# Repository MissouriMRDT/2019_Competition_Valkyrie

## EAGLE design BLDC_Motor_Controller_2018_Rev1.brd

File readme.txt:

https://www.amazon.com/RunCam-Camera-600TVL-Blocked-Quadcopter/dp/B06XW93GM9/ref=sr_1_5?s=electronics&ie=UTF8&qid=1522101421&sr=1-5&keywords=runcam

/////////////////////////////////////////////////////////////
// 3 Pin Picoblade twisted pair FPV:

// 1 => yellow => composite video (0.000v to 1.073v peak)
// 2 => black  => ground (0v)
// 3 => red    => 12v

/////////////////////////////////////////////////////////////
// 2 Pin BNC video:

// 1 => tip => composite video (0.000v to 1.073v peak)
// 2 => sleeve  => ground (0v)

https://www.digikey.com/product-detail/en/te-connectivity-amp-connectors/1-1478032-0/A97560-ND/1755947

/////////////////////////////////////////////////////////////
// 2 Pin RCA video (yellow)

// 1 => tip => composite video (0.000v to 1.073v peak)
// 2 => sleeve  => ground (0v)

https://www.digikey.com/product-detail/en/switchcraft-inc/PJRAN1X1U04X/PJRAN1X1U04X-ND/969899
http://www.switchcraft.com/Drawings/pjran1x1u__x_series_cd.pdf

/////////////////////////////////////////////////////////////
// 2 Pin barrel jack (2.1mm by 5.5mm center positive)

// 1 => center => 12v positive
// 2 => sleeve  => ground (0v)

https://www.digikey.com/product-detail/en/mpd-memory-protection-devices/EJ508A/EJ508A-ND/2439547

////////////////////////////////////////////////////////////////////////////////////////////////////

https://www.digikey.com/product-detail/en/texas-instruments/LMH6574MA-NOPB/LMH6574MA-NOPB-ND/700454
https://www.digikey.com/product-detail/en/texas-instruments/TXB0102DCUR/296-22862-1-ND/1740009

http://www.ti.com/lit/ds/symlink/lmh6574.pdf
http://www.ti.com/lit/ds/symlink/txb0102.pdf

//////////////////////////////////////////////////////////////////////////////////////////////////////////////////////////////

https://www.propwashed.com/quadcopter-connector-guide/
https://www.propwashed.com/fpv-camera-buyers-guide/
https://www.cctv-information.co.uk/i/Transmission_of_Video_Signals

https://www.digikey.com/en/ptm/t/texas-instruments/introduction-to-level-translation/tutorial
https://www.digikey.com/en/ptm/t/texas-instruments/amplifiers-high-speed-amplifiers-for-video-applications---part-1/tutorial
https://www.digikey.com/en/ptm/t/texas-instruments/amplifiers-high-speed-amplifiers-for-video-applications---part-2/tutorial
https://www.digikey.com/en/ptm/t/texas-instruments/amplifiers-high-speed-amplifiers-for-video-applications---part-3/tutorial

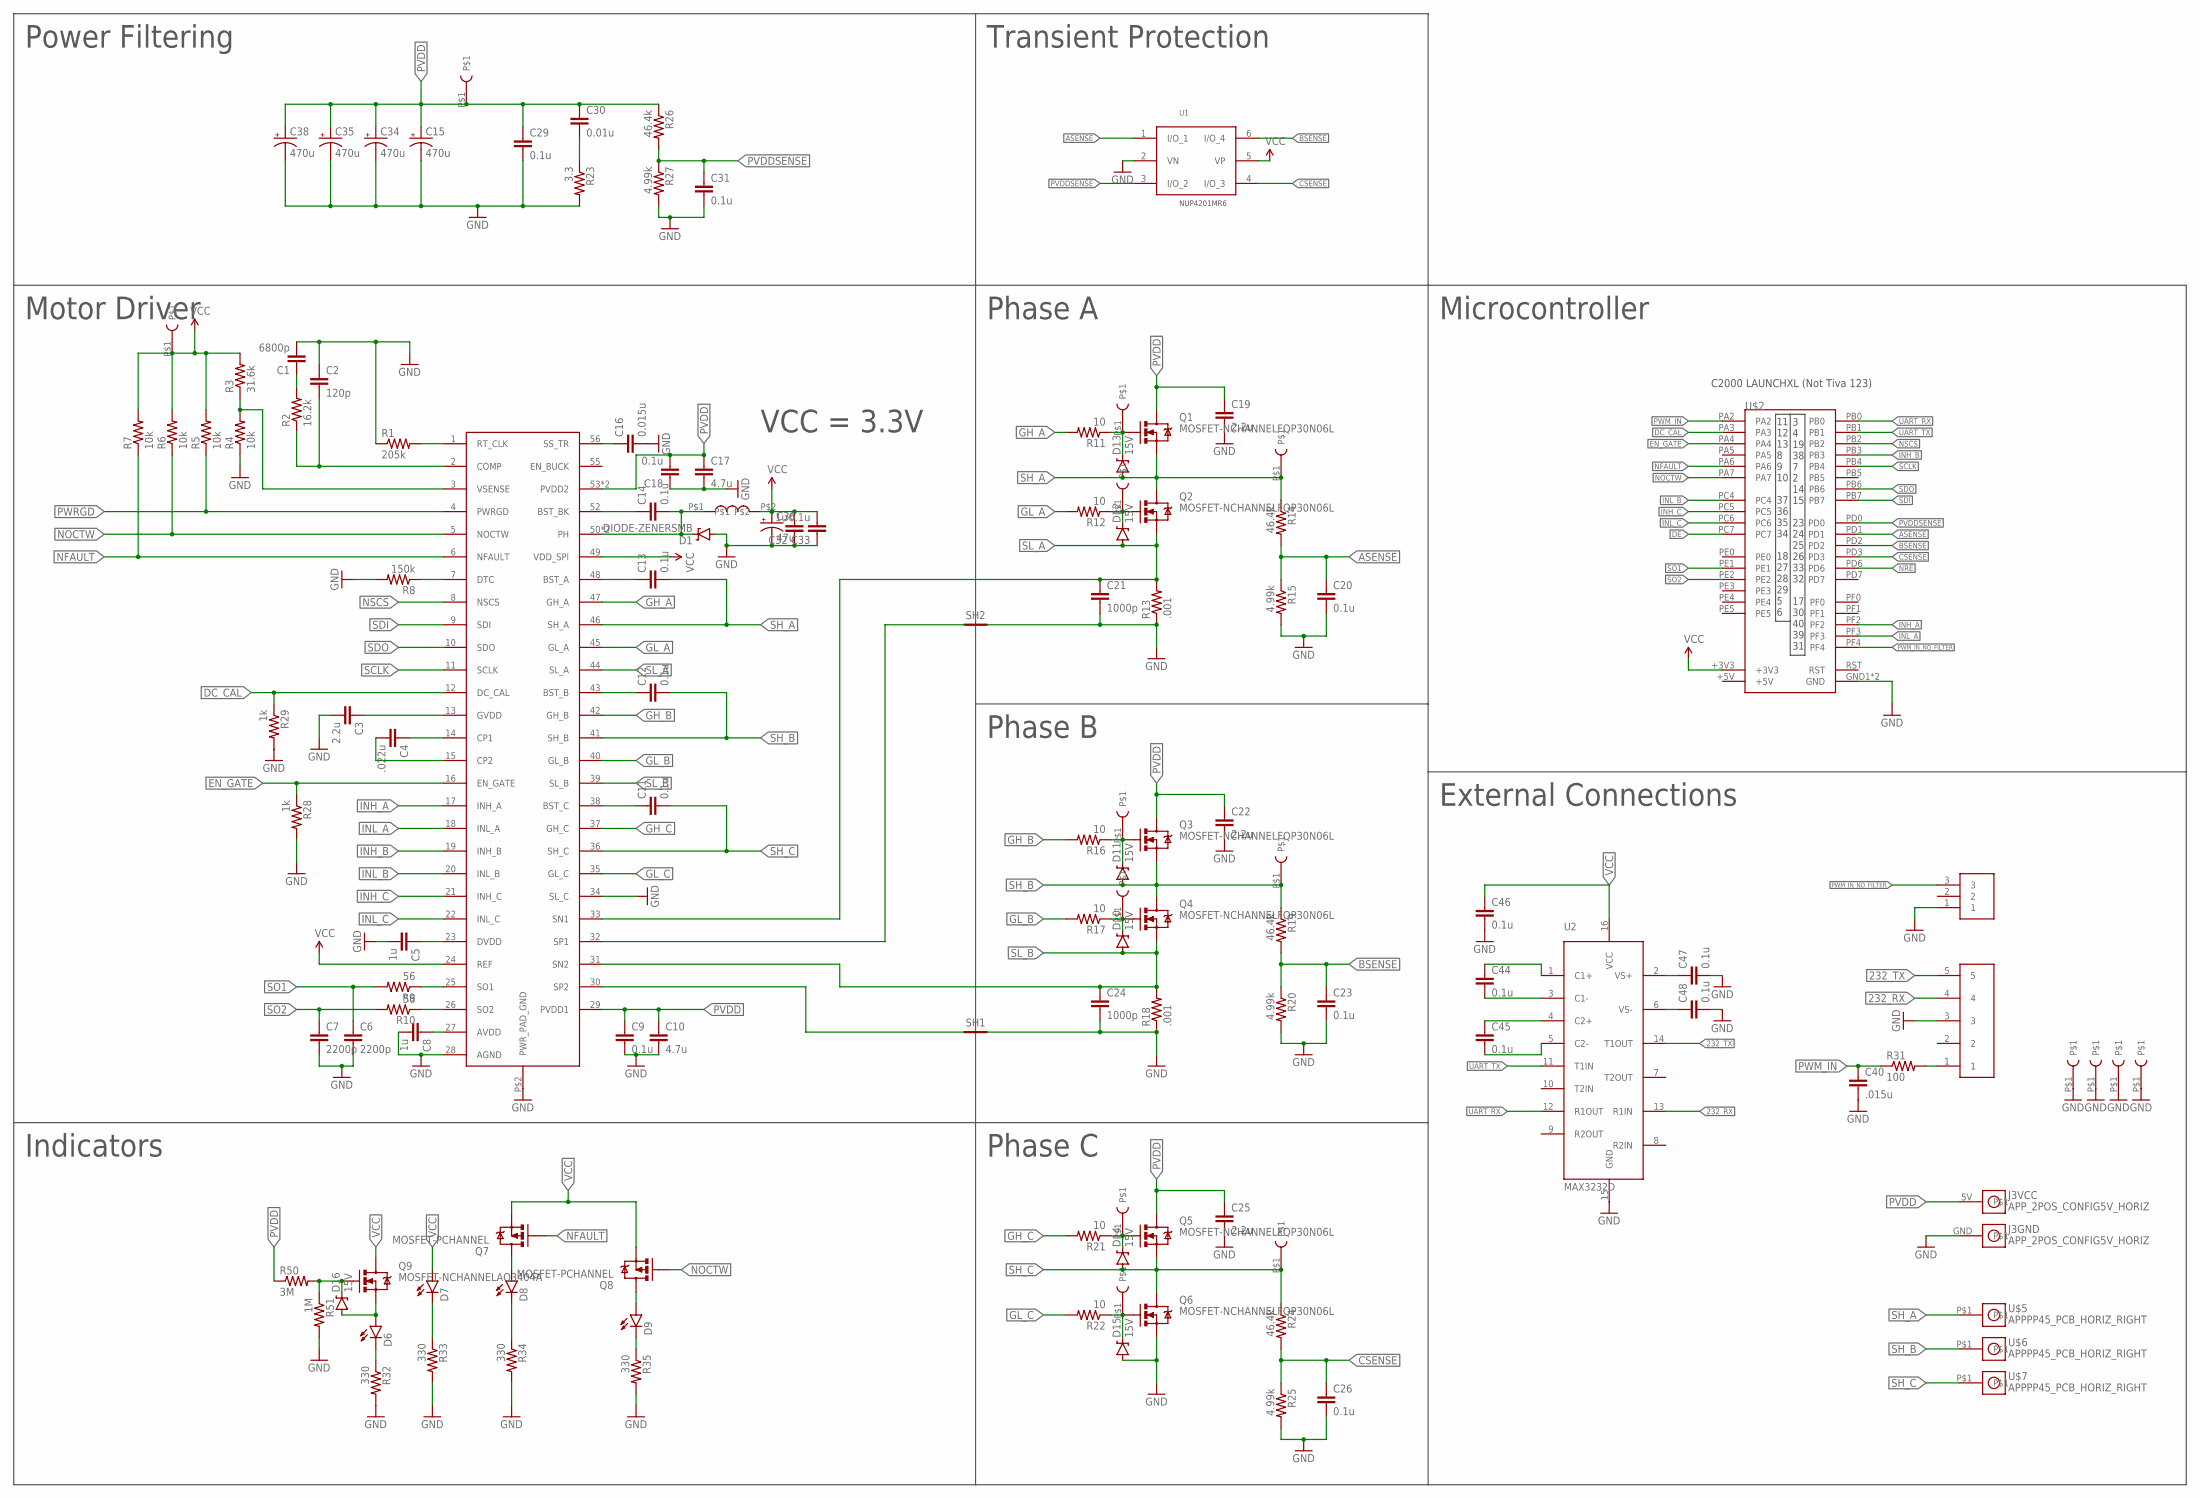
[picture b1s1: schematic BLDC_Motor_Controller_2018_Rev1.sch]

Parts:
C1: 6800p; 0805
C2: 120p; 0805
C3, C19, C22, C25: 2.2u; 1206
C4: .022u; 0805
C5, C8, C32: 1u; 0805
C6, C7: 2200p; 0805
C9, C11, C12, C13, C14, C18, C20, C23, C26, C29, C31, C33, C44, C45, C46, C47, C48: 0.1u; 0805
C10, C17: 4.7u; 1206
C15, C34, C35, C38: 470u; CPOL-RADIAL-1000UF-25V
C16: 0.015u; 0805
C21, C24: 1000p; 0805
C30: 0.01u; 0805
C36: 47u; CPOL-RADIAL-100UF-25V
C40: .015u; 0805
D1: DIODE-ZENERSMB; SMB-DIODE
D6, D7, D8, D9: LED1206; LED-1206
D10, D11, D12, D13, D14, D15, D16: 15V; SOD-323
J1: SL03THROUGH_HOLE; MOLEX_SL_03_TH
J3: APP_2POS_CONFIG5V_HORIZ; APP45_5V_HORIZ_CONFIG
Q1, Q2, Q3, Q4, Q5, Q6: MOSFET-NCHANNELFQP30N06L; TO220V
Q7, Q8: MOSFET-PCHANNEL; SOT23-3
Q9: MOSFET-NCHANNELAO3404A; SOT23-3
R1: 205k; 0805
R2: 16.2k; 0805
R3: 31.6k; 0805
R4, R5, R6, R7: 10k; 0805
R8: 150k; 0805
R9, R10: 56; 0805
R11, R12, R16, R17, R21, R22: 10; 0805
R13, R18: .001; 1206
R14, R19, R24, R26: 46.4k; 0805
R15, R20, R25, R27: 4.99k; 0805
R23: 3.3; 0805
R28, R29: 1k; 0805
R31: 100; 0805
R32, R33, R34, R35: 330; 0805
R50: 3M; 0805
R51: 1M; 0805
SH1, SH2: SHORT-HT5; SHORT_TOP-50
U1: NUP4201MR6; TSOP-6
U2: MAX3232D; SOIC16
U$1: DRV8301; DCA
U$2: TIVA-C
U$4: 5PIN
U$5, U$6, U$7: APPPP45_PCB_HORIZ_RIGHT; APP45_PCB_HORIZ_RIGHT
U$10, U$11, U$12, U$15, U$16, U$17, U$18, U$19, U$20, U$24, U$25, U$26, U$27, U$28, U$29: TEST_POINT_0.1INDIAM
U$14: 33u; INDUCTOR_DR74

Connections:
232_RX: U2.13 (R1IN), U$4.4
232_TX: U2.14 (T1OUT), U$4.5
+5V: U$2.+5V
ASENSE: C20.1, R14.2, R15.1, U1.1 (I/O_1), U$2.PD1
BSENSE: C23.1, R19.2, R20.1, U1.6 (I/O_4), U$2.PD2
CSENSE: C26.1, R24.2, R25.1, U1.4 (I/O_3), U$2.PD3
DC_CAL: R29.1, U$1.12 (DC_CAL), U$2.PA3
DE: U$2.PC7
EN_GATE: R28.1, U$1.16 (EN_GATE), U$2.PA4
GH_A: R11.2, U$1.47 (GH_A)
GH_B: R16.2, U$1.42 (GH_B)
GH_C: R21.2, U$1.37 (GH_C)
GL_A: R12.2, U$1.45 (GL_A)
GL_B: R17.2, U$1.40 (GL_B)
GL_C: R22.2, U$1.35 (GL_C)
GND: C1.2, C2.1, C3.2, C5.2, C6.2, C7.2, C8.2, C9.2, C10.2, C15.2 (-), C16.2, C17.2, C18.1, C19.2, C20.2, C21.2, C22.2, C23.2, C24.2, C25.2, C26.2, C29.2, C31.2, C32.1, C33.1, C34.2 (-), C35.2 (-), C36.2 (-), C38.2 (-), C40.2, C46.2, C47.2, C48.2, D1.A, D15.A, J1.1, J3.GND, Q6.3 (S), R1.1, R4.1, R8.2, R13.1, R15.2, R18.1, R20.2, R23.2, R25.2, R27.2, R28.2, R29.2, R32.2, R33.2, R34.2, R35.2, R51.2, SH1.2, SH2.2, U1.2 (VN), U2.15 (GND), U$1.28 (AGND), U$1.34 (SL_C), U$1.P$2 (PWR_PAD_GND), U$2.GND1 (GND), U$2.GND2 (GND), U$4.3, U$26.P$1, U$27.P$1, U$28.P$1, U$29.P$1
INH_A: U$1.17 (INH_A), U$2.PF2
INH_B: U$1.19 (INH_B), U$2.PB3
INH_C: U$1.21 (INH_C), U$2.PC5
INL_A: U$1.18 (INL_A), U$2.PF3
INL_B: U$1.20 (INL_B), U$2.PC4
INL_C: U$1.22 (INL_C), U$2.PC6
unnamed: C2.2, R2.1, U$1.2 (COMP)
unnamed: C1.1, R2.2
unnamed: R3.1, R4.2, U$1.3 (VSENSE)
unnamed: R1.2, U$1.1 (RT_CLK)
unnamed: R8.1, U$1.7 (DTC)
unnamed: C4.1, U$1.14 (CP1)
unnamed: C4.2, U$1.15 (CP2)
unnamed: C3.1, U$1.13 (GVDD)
unnamed: C5.1, U$1.23 (DVDD)
unnamed: R9.1, U$1.25 (SO1)
unnamed: R10.1, U$1.26 (SO2)
unnamed: C8.1, U$1.27 (AVDD)
unnamed: D13.C, Q1.1 (G), R11.1, U$12.P$1
unnamed: D11.C, Q3.1 (G), R16.1, U$16.P$1
unnamed: D10.C, Q4.1 (G), R17.1, U$17.P$1
unnamed: D12.C, Q2.1 (G), R12.1, U$15.P$1
unnamed: D14.C, Q5.1 (G), R21.1, U$18.P$1
unnamed: D15.C, Q6.1 (G), R22.1, U$19.P$1
unnamed: C11.1, U$1.38 (BST_C)
unnamed: C30.2, R23.1
unnamed: D6.C, R32.1
unnamed: D7.C, R33.1
unnamed: C12.1, U$1.43 (BST_B)
unnamed: D8.C, R34.1
unnamed: D9.C, R35.1
unnamed: D9.A, Q8.3 (D)
unnamed: C13.1, U$1.48 (BST_A)
unnamed: C14.1, U$1.52 (BST_BK)
unnamed: C14.2, D1.C, U$1.50 (PH), U$1.51 (PH), U$14.P$1
unnamed: D8.A, Q7.3 (D)
unnamed: R31.2, U$4.1
unnamed: C16.1, U$1.56 (SS_TR)
unnamed: D16.C, Q9.1 (G), R50.2, R51.1
unnamed: C44.1, U2.1 (C1+)
unnamed: D6.A, D16.A, Q9.2 (S)
unnamed: C44.2, U2.3 (C1-)
unnamed: C45.1, U2.4 (C2+)
unnamed: C45.2, U2.5 (C2-)
unnamed: C48.1, U2.6 (VS-)
unnamed: C47.1, U2.2 (VS+)
NFAULT: Q7.1 (G), R7.1, U$1.6 (NFAULT), U$2.PA6
NOCTW: Q8.1 (G), R6.1, U$1.5 (NOCTW), U$2.PA7
NRE: U$2.PD6
NSCS: U$1.8 (NSCS), U$2.PB2
PVDD: C9.1, C10.1, C15.1 (+), C17.1, C18.2, C19.1, C22.1, C25.1, C29.1, C30.1, C34.1 (+), C35.1 (+), C38.1 (+), J3.5V, Q1.2 (D), Q3.2 (D), Q5.2 (D), R26.1, R50.1, U$1.29 (PVDD1), U$1.53 (PVDD2), U$1.54 (PVDD2), U$11.P$1
PVDDSENSE: C31.1, R26.2, R27.1, U1.3 (I/O_2), U$2.PD0
PWM_IN: C40.1, R31.1, U$2.PA2
PWM_IN_NO_FILTER: J1.3, U$2.PF4
PWRGD: R5.1, U$1.4 (PWRGD)
RST: U$2.RST
SCLK: U$1.11 (SCLK), U$2.PB4
SDI: U$1.9 (SDI), U$2.PB7
SDO: U$1.10 (SDO), U$2.PB6
SH_A: C13.2, D13.A, Q1.3 (S), Q2.2 (D), R14.1, U$1.46 (SH_A), U$5.P$1, U$25.P$1
SH_B: C12.2, D11.A, Q3.3 (S), Q4.2 (D), R19.1, U$1.41 (SH_B), U$6.P$1, U$24.P$1
SH_C: C11.2, D14.A, Q5.3 (S), Q6.2 (D), R24.1, U$1.36 (SH_C), U$7.P$1, U$20.P$1
SL_A: C21.1, D12.A, Q2.3 (S), R13.2, U$1.33 (SN1), U$1.44 (SL_A)
SL_B: C24.1, D10.A, Q4.3 (S), R18.2, U$1.31 (SN2), U$1.39 (SL_B)
SO1: C6.1, R9.2, U$2.PE1
SO2: C7.1, R10.2, U$2.PE2
SP1: SH2.1, U$1.32 (SP1)
SP2: SH1.1, U$1.30 (SP2)
UART_RX: U2.12 (R1OUT), U$2.PB0
UART_TX: U2.11 (T1IN), U$2.PB1
VCC: C32.2, C33.2, C36.1 (+), C46.1, D7.A, Q7.2 (S), Q8.2 (S), Q9.3 (D), R3.2, R5.2, R6.2, R7.2, U1.5 (VP), U2.16 (VCC), U$1.24 (REF), U$1.49 (VDD_SPI), U$2.+3V3, U$10.P$1, U$14.P$2

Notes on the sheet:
11 12 13 8 9 10 37 36 35 34 18 27 28 29 5 6
3 4 19 38 7 2 14 15 23 24 25 26 33 32 17 30 40 39 31
C2000 LAUNCHXL (Not Tiva 123)
Power Filtering
Motor Driver
Transient Protection
Phase A
Phase B
Phase C
Microcontroller
External Connections
Indicators
VCC = 3.3V

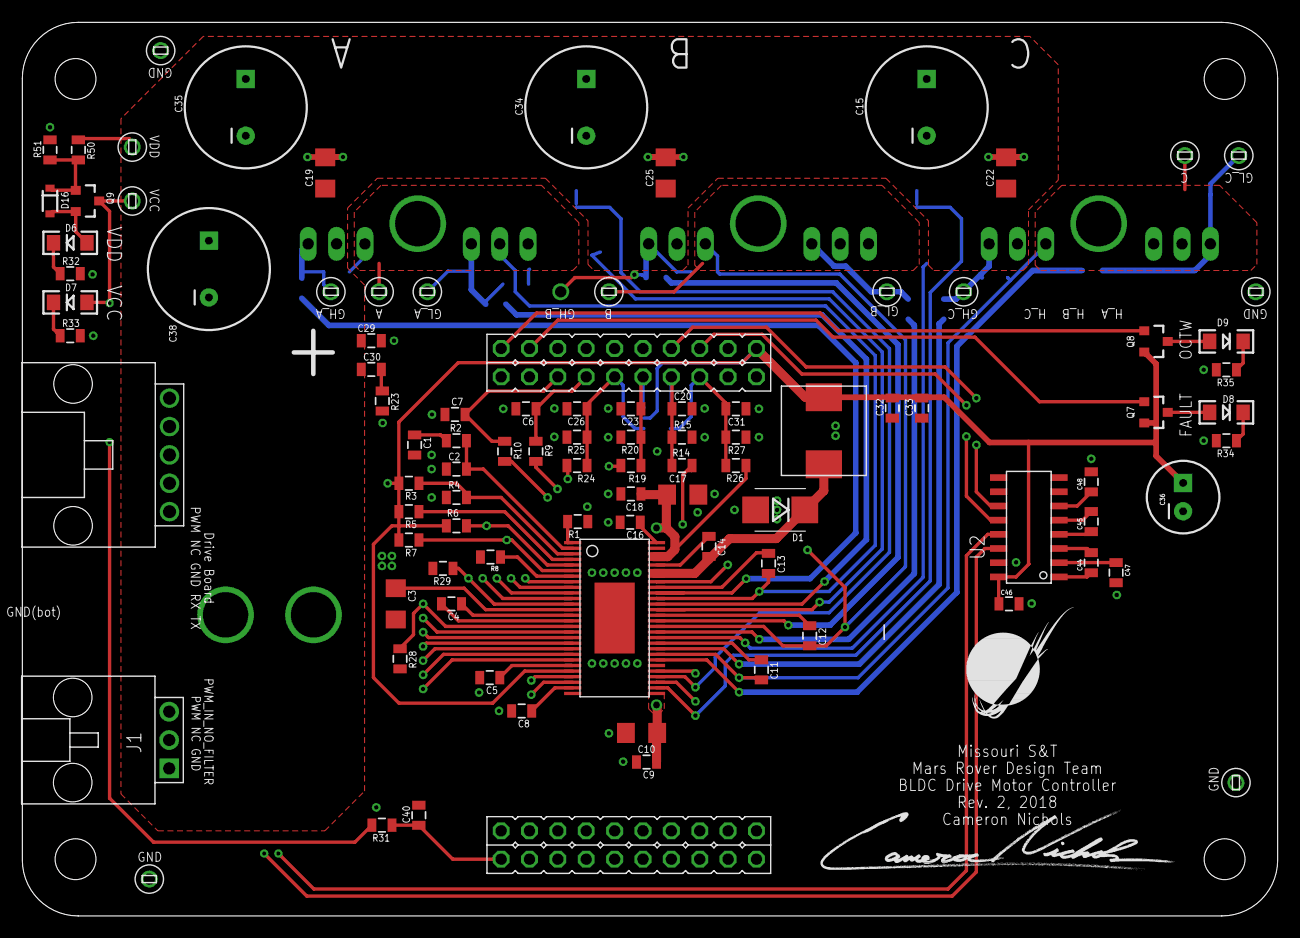
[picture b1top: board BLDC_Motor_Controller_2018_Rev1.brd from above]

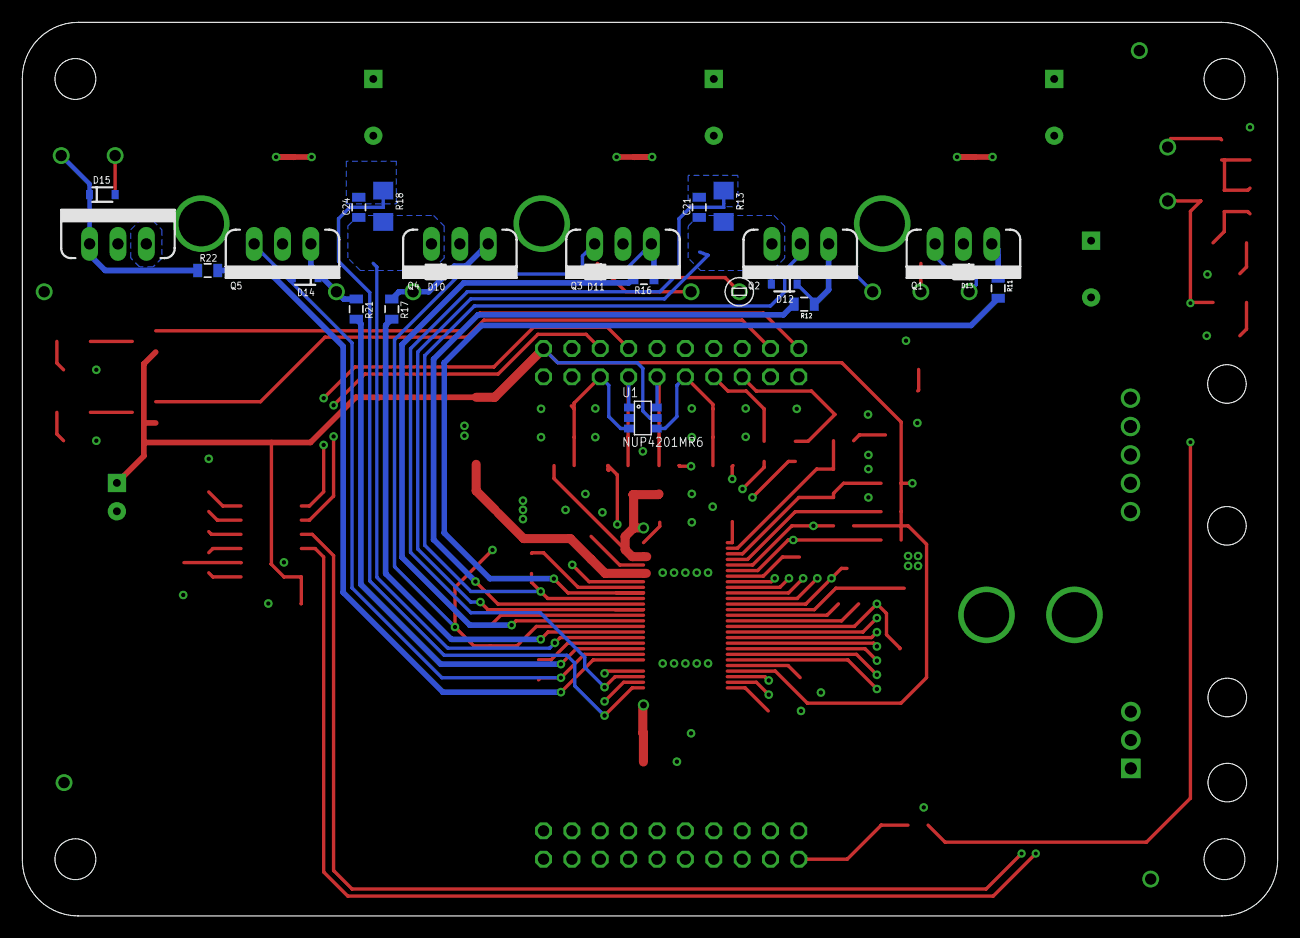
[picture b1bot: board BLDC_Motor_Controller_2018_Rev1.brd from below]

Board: 4 copper layers, 112.4 x 80.0 mm, 127 parts (26 on the bottom side), 83 nets.

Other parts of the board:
U$9: MRDT_LOGO

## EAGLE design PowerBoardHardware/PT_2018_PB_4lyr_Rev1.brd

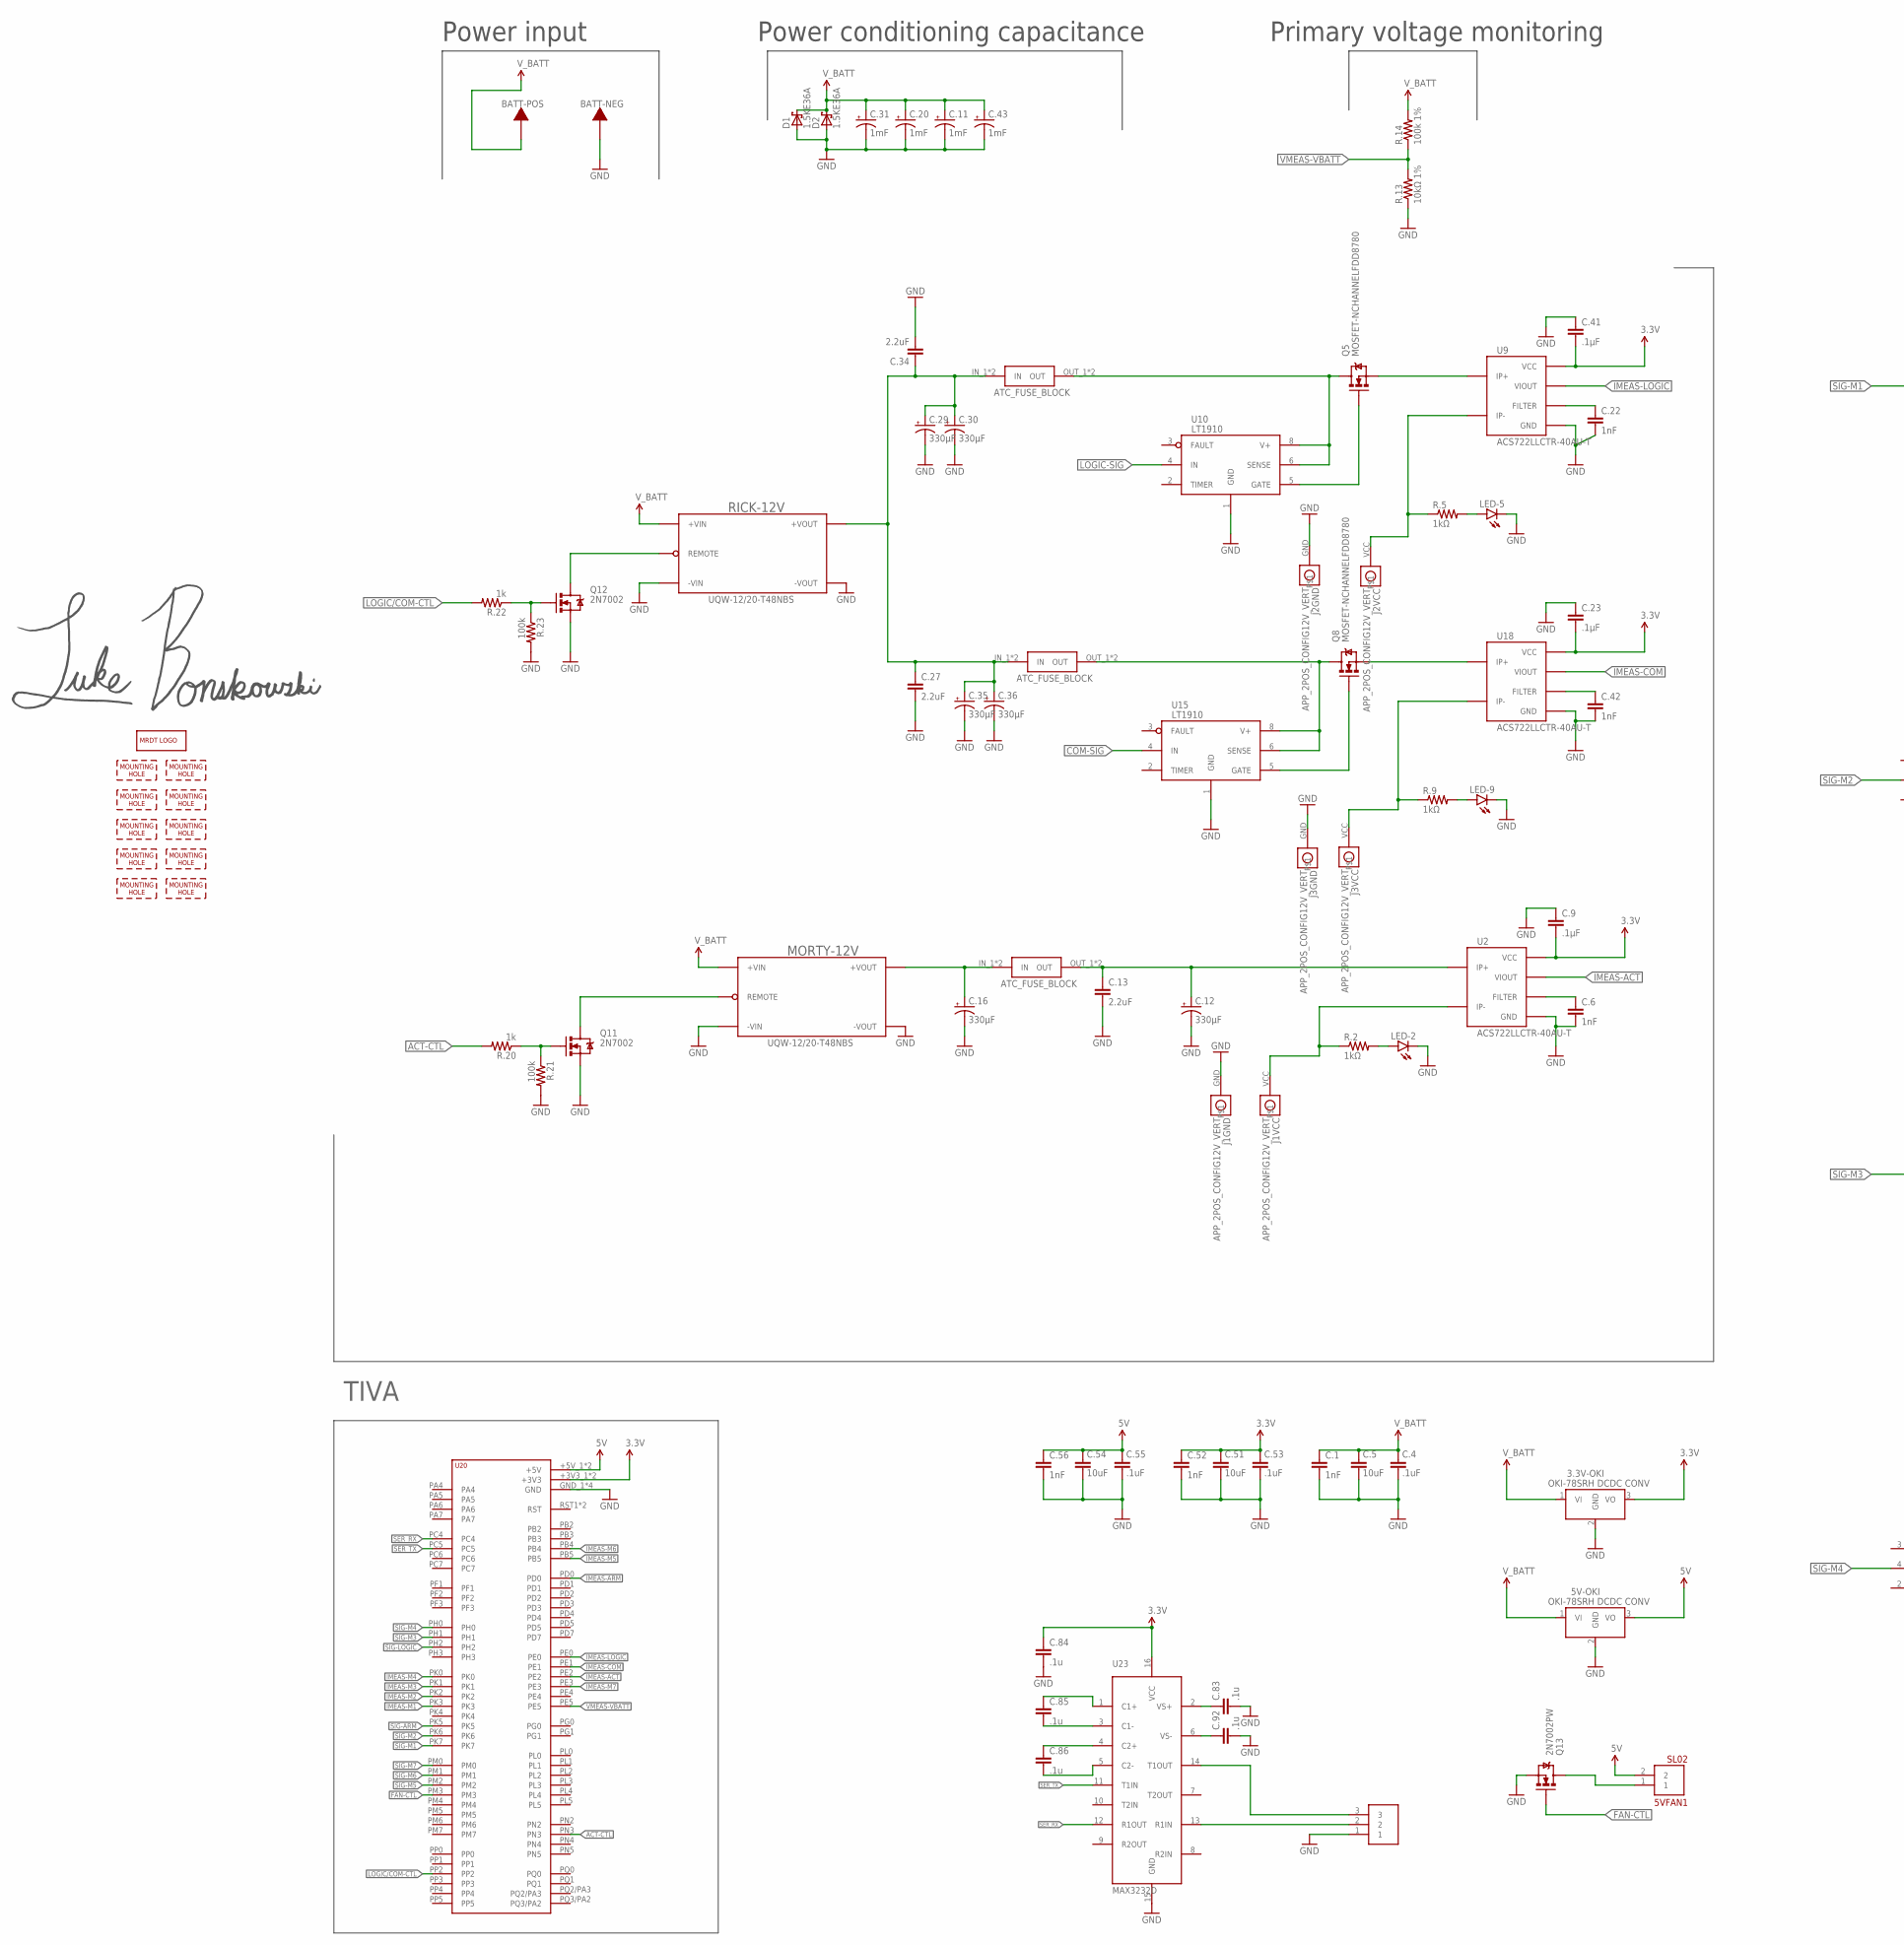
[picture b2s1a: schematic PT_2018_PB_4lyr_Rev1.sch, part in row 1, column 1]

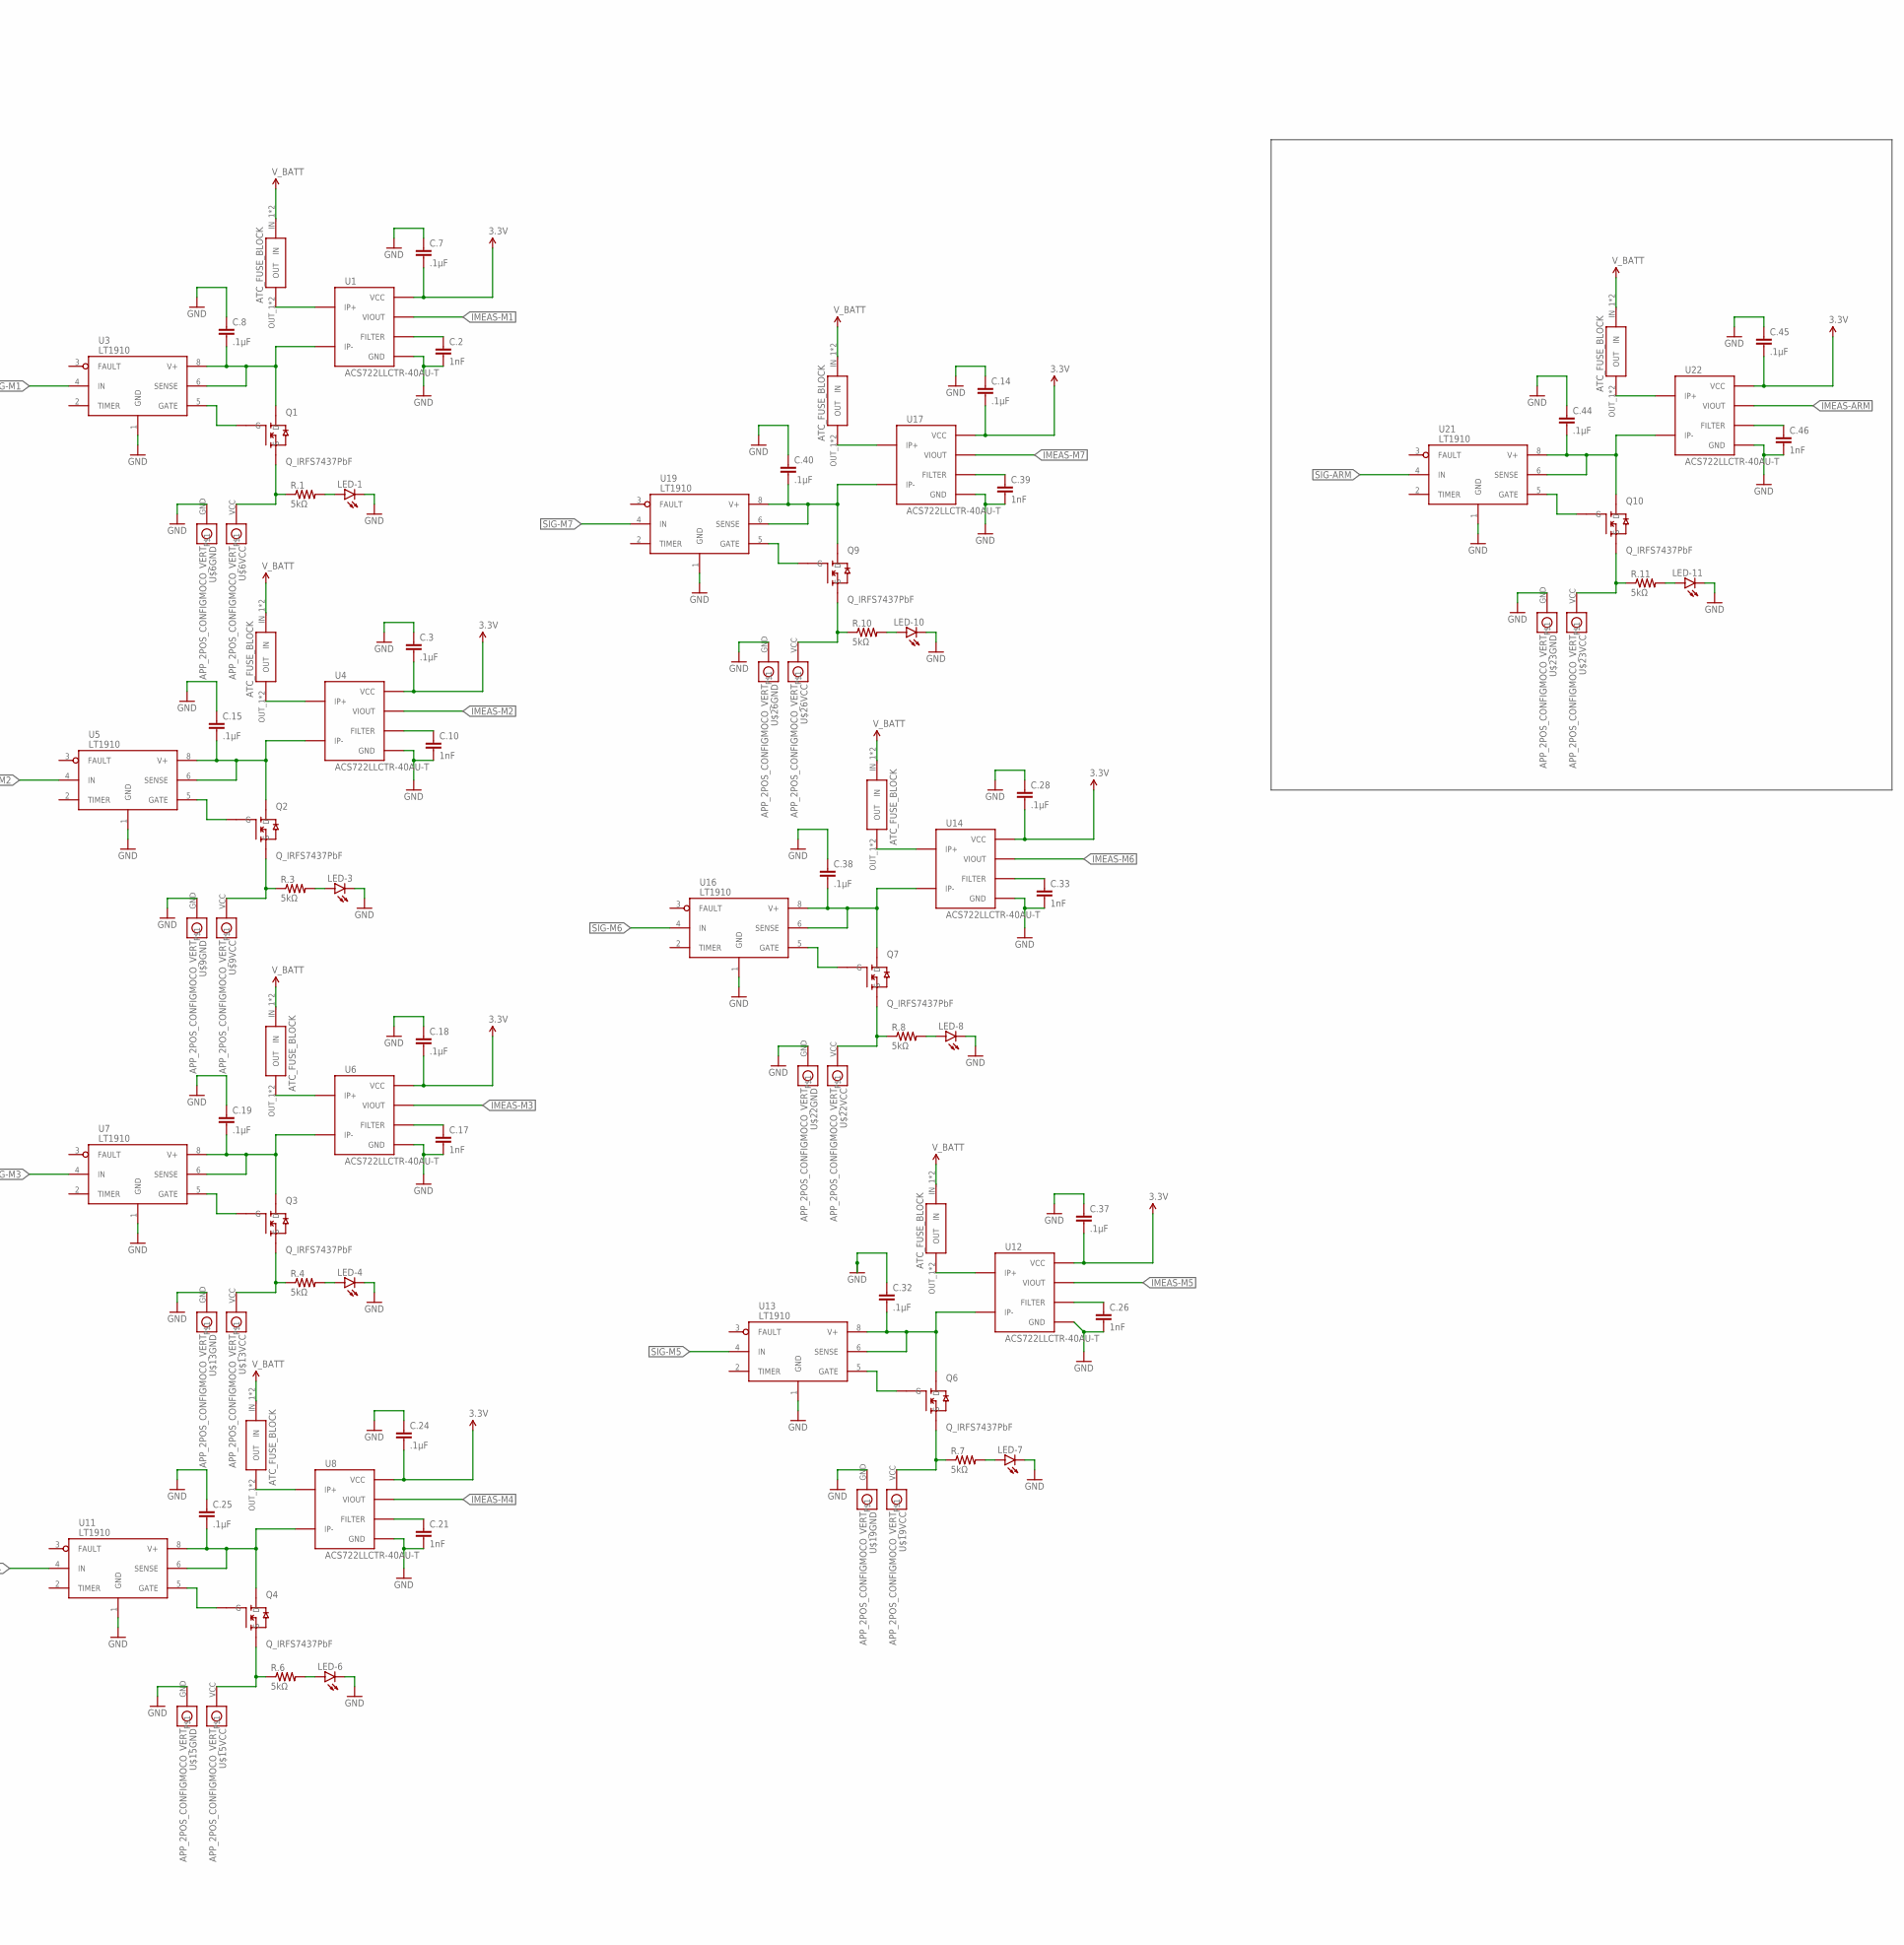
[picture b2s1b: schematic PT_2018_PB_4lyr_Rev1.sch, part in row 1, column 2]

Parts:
3.3V-OKI, 5V-OKI: Q_OKI-78SR; OKI-78SR_HORIZ
5VFAN1: SL02; MOLEX-70543-0001
BATT-NEG: TERMINAL_HOLE; LARGE_TERMINAL_HOLE
BATT-POS: TERMINAL_HOLE; LARGE_TERMINAL_HOLE
BMS_SERIAL: SL03; MOLEX-70543-0002
C.1, C.2, C.6, C.10, C.17, C.21, C.22, C.26, C.33, C.39, C.42, C.46, C.52, C.56: 1nF; 0805
C.3, C.7, C.8, C.9, C.14, C.15, C.18, C.19, C.23, C.24, C.25, C.28, C.32, C.37, C.38, C.40, C.41, C.44, C.45: .1µF; 0805
C.4, C.53, C.55: .1uF; 0805
C.5, C.51, C.54: 10uF; 1206
C.11, C.20, C.31, C.43: 1mF; C_12.5MM
C.12, C.16, C.29, C.30, C.35, C.36: 330µF; E5-8,5
C.13, C.27, C.34: 2.2uF; 1206
C.83, C.84, C.85, C.86, C.92: .1u; 0805
D1, D2: 1.5KE36A; CB429-17
J1, J2, J3: APP_2POS_CONFIG12V_VERT; APP45_12V_VERT_CONFIG
LED-1, LED-2, LED-3, LED-4, LED-5, LED-6, LED-7, LED-8, LED-9, LED-10, LED-11: LED1206; LED-1206
MORTY-12V: UQW-12/20-T48NBS; U-T48-QB-NO_TRIM
Q1, Q2, Q3, Q4, Q6, Q7, Q9, Q10: Q_IRFS7437PbF; D2PACK
Q5, Q8: MOSFET-NCHANNELFDD8780; DPAK
Q11, Q12: 2N7002; SOT323
Q13: 2N7002PW; SOT323
R.1, R.3, R.4, R.6, R.7, R.8, R.10, R.11: 5kΩ; 1206
R.2, R.5, R.9: 1kΩ; 1206
R.13: 10kΩ 1%; R1206
R.14: 100k 1%; R1206
R.20, R.22: 1k; R1206
R.21, R.23: 100k; R1206
RICK-12V: UQW-12/20-T48NBS; U-T48-QB-NO_TRIM
U1, U2, U4, U6, U8, U9, U12, U14, U17, U18, U22: ACS722LLCTR-40AU-T; SOIC8_ACS711
U3, U5, U7, U10, U11, U13, U15, U16, U19, U21: LT1910; SO8
U20: TIVA-1294; TIVA-C-CONNECTED
U23: MAX3232D; SOIC16
U$1, U$2, U$3, U$4, U$12, U$18, U$24, U$28, U$30, U$31: MOUNTING_HOLE#6; #6_SCREW
U$5, U$7, U$10, U$11, U$14, U$16, U$17, U$20, U$21, U$25, U$29: ATC_FUSE_BLOCK; BLOCK_3557-2
U$6, U$9, U$13, U$15, U$19, U$22, U$23, U$26: APP_2POS_CONFIGMOCO_VERT; APP45_MOCO_VERT_CONFIG
U$8: MRDT_LOGO
U$27: LUCAS_BONSKOWSKI_SIGNATURE

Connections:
3.3V: 3.3V-OKI.3 (VO), C.3.2, C.7.2, C.9.2, C.14.2, C.18.2, C.23.2, C.24.2, C.28.2, C.37.2, C.41.2, C.45.2, C.51.1, C.52.1, C.53.1, C.84.1, U1.8 (VCC), U2.8 (VCC), U4.8 (VCC), U6.8 (VCC), U8.8 (VCC), U9.8 (VCC), U12.8 (VCC), U14.8 (VCC), U17.8 (VCC), U18.8 (VCC), U20.+3V3_1 (+3V3), U20.+3V3_2 (+3V3), U22.8 (VCC), U23.16 (VCC)
5V: 5V-OKI.3 (VO), 5VFAN1.2, C.54.1, C.55.1, C.56.1, U20.+5V_1 (+5V), U20.+5V_2 (+5V)
12V-AUX-ACT: J1.VCC, R.2.1, U2.4 (IP-)
12V-AUX-COM: J3.VCC, R.9.1, U18.4 (IP-)
12V-AUX-LOGIC: J2.VCC, R.5.1, U9.4 (IP-)
232_RX: BMS_SERIAL.2, U23.13 (R1IN)
232_TX: BMS_SERIAL.3, U23.14 (T1OUT)
ACT-CTL: R.20.2, U20.PN3
COM-SIG: U15.4 (IN)
DRAIN-ARM: C.44.2, Q10.TAB (D), U21.6 (SENSE), U21.8 (V+), U22.4 (IP-)
DRAIN-M1: C.8.2, Q1.TAB (D), U1.4 (IP-), U3.6 (SENSE), U3.8 (V+)
DRAIN-M2: C.15.2, Q2.TAB (D), U4.4 (IP-), U5.6 (SENSE), U5.8 (V+)
DRAIN-M3: C.19.2, Q3.TAB (D), U6.4 (IP-), U7.6 (SENSE), U7.8 (V+)
DRAIN-M4: C.25.2, Q4.TAB (D), U8.4 (IP-), U11.6 (SENSE), U11.8 (V+)
DRAIN-M5: C.32.2, Q6.TAB (D), U12.4 (IP-), U13.6 (SENSE), U13.8 (V+)
DRAIN-M6: C.38.2, Q7.TAB (D), U14.4 (IP-), U16.6 (SENSE), U16.8 (V+)
DRAIN-M7: C.40.2, Q9.TAB (D), U17.4 (IP-), U19.6 (SENSE), U19.8 (V+)
FAN-CTL: Q13.1 (G), U20.PM3
FILTER-ARM: C.46.1, U22.6 (FILTER)
FILTER-M1: C.2.1, U1.6 (FILTER)
FILTER-M2: C.10.1, U4.6 (FILTER)
FILTER-M3: C.17.1, U6.6 (FILTER)
FILTER-M4: C.21.1, U8.6 (FILTER)
FILTER-M5: C.26.1, U12.6 (FILTER)
FILTER-M6: C.33.1, U14.6 (FILTER)
FILTER-M7: C.39.1, U17.6 (FILTER)
GATE-ARM: Q10.1 (G), U21.5 (GATE)
GATE-M1: Q1.1 (G), U3.5 (GATE)
GATE-M2: Q2.1 (G), U5.5 (GATE)
GATE-M3: Q3.1 (G), U7.5 (GATE)
GATE-M4: Q4.1 (G), U11.5 (GATE)
GATE-M5: Q6.1 (G), U13.5 (GATE)
GATE-M6: Q7.1 (G), U16.5 (GATE)
GATE-M7: Q9.1 (G), U19.5 (GATE)
GND: 3.3V-OKI.2 (GND), 5V-OKI.2 (GND), BATT-NEG.P$1, BMS_SERIAL.1, C.1.2, C.2.2, C.3.1, C.4.2, C.5.2, C.6.2, C.7.1, C.8.1, C.9.1, C.10.2, C.11.-, C.12.-, C.13.2, C.14.1, C.15.1, C.16.-, C.17.2, C.18.1, C.19.1, C.20.-, C.21.2, C.22.2, C.23.1, C.24.1, C.25.1, C.26.2, C.27.2, C.28.1, C.29.-, C.30.-, C.31.-, C.32.1, C.33.2, C.34.2, C.35.-, C.36.-, C.37.1, C.38.1, C.39.2, C.40.1, C.41.1, C.42.2, C.43.-, C.44.1, C.45.1, C.46.2, C.51.2, C.52.2, C.53.2, C.54.2, C.55.2, C.56.2, C.83.2, C.84.2, C.92.2, D1.A, D2.A, J1.GND, J2.GND, J3.GND, LED-1.C, LED-2.C, LED-3.C, LED-4.C, LED-5.C, LED-6.C, LED-7.C, LED-8.C, LED-9.C, LED-10.C, LED-11.C, MORTY-12V.3 (-VIN), MORTY-12V.4 (-VOUT), Q11.2 (S), Q12.2 (S), Q13.2 (S), R.13.1, R.21.2, R.23.2, RICK-12V.3 (-VIN), RICK-12V.4 (-VOUT), U1.5 (GND), U2.5 (GND), U3.1 (GND), U4.5 (GND), U5.1 (GND), U6.5 (GND), U7.1 (GND), U8.5 (GND), U9.5 (GND), U10.1 (GND), U11.1 (GND), U12.5 (GND), U13.1 (GND), U14.5 (GND), U15.1 (GND), U16.1 (GND), U17.5 (GND), U18.5 (GND), U19.1 (GND), U20.GND_1 (GND), U20.GND_2 (GND), U20.GND_3 (GND), U20.GND_4 (GND), U21.1 (GND), U22.5 (GND), U23.15 (GND), U$6.GND, U$9.GND, U$13.GND, U$15.GND, U$19.GND, U$22.GND, U$23.GND, U$26.GND
IMEAS-ACT: U2.7 (VIOUT), U20.PE2
IMEAS-ARM: U20.PD0, U22.7 (VIOUT)
IMEAS-COM: U18.7 (VIOUT), U20.PE1
IMEAS-LOGIC: U9.7 (VIOUT), U20.PE0
IMEAS-M1: U1.7 (VIOUT), U20.PK3
IMEAS-M2: U4.7 (VIOUT), U20.PK2
IMEAS-M3: U6.7 (VIOUT), U20.PK1
IMEAS-M4: U8.7 (VIOUT), U20.PK0
IMEAS-M5: U12.7 (VIOUT), U20.PB5
IMEAS-M6: U14.7 (VIOUT), U20.PB4
IMEAS-M7: U17.7 (VIOUT), U20.PE3
LEDLINE-ARM: LED-11.A, R.11.2
LEDLINE-M1: LED-1.A, R.1.2
LEDLINE-M2: LED-3.A, R.3.2
LEDLINE-M3: LED-4.A, R.4.2
LEDLINE-M4: LED-6.A, R.6.2
LEDLINE-M5: LED-7.A, R.7.2
LEDLINE-M6: LED-8.A, R.8.2
LEDLINE-M7: LED-10.A, R.10.2
LOGIC-SIG: U10.4 (IN)
LOGIC/COM-CTL: R.22.2, U20.PP2
unnamed: C.16.+, MORTY-12V.8 (+VOUT), U$7.IN_1 (IN), U$7.IN_2 (IN)
unnamed: Q12.3 (D), RICK-12V.2 (REMOTE)
unnamed: C.22.1, U9.6 (FILTER)
unnamed: 5VFAN1.1, Q13.3 (D)
unnamed: LED-2.A, R.2.2
unnamed: LED-9.A, R.9.2
unnamed: MORTY-12V.2 (REMOTE), Q11.3 (D)
unnamed: C.27.1, C.29.+, C.30.+, C.34.1, C.35.+, C.36.+, RICK-12V.8 (+VOUT), U$16.IN_1 (IN), U$16.IN_2 (IN), U$20.IN_1 (IN), U$20.IN_2 (IN)
unnamed: C.83.1, U23.2 (VS+)
unnamed: C.6.1, U2.6 (FILTER)
unnamed: C.42.1, U18.6 (FILTER)
unnamed: LED-5.A, R.5.2
unnamed: Q8.1 (G), U15.5 (GATE)
unnamed: C.12.+, C.13.1, U2.1 (IP+), U$7.OUT_1 (OUT), U$7.OUT_2 (OUT)
unnamed: Q8.3 (S), U18.1 (IP+)
unnamed: Q8.4 (D), U15.6 (SENSE), U15.8 (V+), U$20.OUT_1 (OUT), U$20.OUT_2 (OUT)
unnamed: Q5.4 (D), U10.6 (SENSE), U10.8 (V+), U$16.OUT_1 (OUT), U$16.OUT_2 (OUT)
unnamed: Q5.3 (S), U9.1 (IP+)
unnamed: Q11.1 (G), R.20.1, R.21.1
unnamed: Q5.1 (G), U10.5 (GATE)
unnamed: C.85.1, U23.1 (C1+)
unnamed: C.85.2, U23.3 (C1-)
unnamed: C.86.1, U23.4 (C2+)
unnamed: C.86.2, U23.5 (C2-)
unnamed: C.92.1, U23.6 (VS-)
unnamed: Q12.1 (G), R.22.1, R.23.1
SER_RX: U20.PC4, U23.12 (R1OUT)
SER_TX: U20.PC5, U23.11 (T1IN)
SIG-ARM: U20.PK5, U21.4 (IN)
SIG-LOGIC: U20.PH2
SIG-M1: U3.4 (IN), U20.PK7
SIG-M2: U5.4 (IN), U20.PK6
SIG-M3: U7.4 (IN), U20.PH1
SIG-M4: U11.4 (IN), U20.PH0
SIG-M5: U13.4 (IN), U20.PM2
SIG-M6: U16.4 (IN), U20.PM1
SIG-M7: U19.4 (IN), U20.PM0
SOURCE-ARM: Q10.2 (S), R.11.1, U$23.VCC
SOURCE-M1: Q1.2 (S), R.1.1, U$6.VCC
SOURCE-M2: Q2.2 (S), R.3.1, U$9.VCC
SOURCE-M3: Q3.2 (S), R.4.1, U$13.VCC
SOURCE-M4: Q4.2 (S), R.6.1, U$15.VCC
SOURCE-M5: Q6.2 (S), R.7.1, U$19.VCC
SOURCE-M6: Q7.2 (S), R.8.1, U$22.VCC
SOURCE-M7: Q9.2 (S), R.10.1, U$26.VCC
VMEAS-VBATT: R.13.2, R.14.1, U20.PE5
V_BATT: 3.3V-OKI.1 (VI), 5V-OKI.1 (VI), BATT-POS.P$1, C.1.1, C.4.1, C.5.1, C.11.+, C.20.+, C.31.+, C.43.+, D1.C, D2.C, MORTY-12V.1 (+VIN), R.14.2, RICK-12V.1 (+VIN), U$5.IN_1 (IN), U$5.IN_2 (IN), U$10.IN_1 (IN), U$10.IN_2 (IN), U$11.IN_1 (IN), U$11.IN_2 (IN), U$14.IN_1 (IN), U$14.IN_2 (IN), U$17.IN_1 (IN), U$17.IN_2 (IN), U$21.IN_1 (IN), U$21.IN_2 (IN), U$25.IN_1 (IN), U$25.IN_2 (IN), U$29.IN_1 (IN), U$29.IN_2 (IN)
V_BATT_ARM: U22.1 (IP+), U$29.OUT_1 (OUT), U$29.OUT_2 (OUT)
V_BATT_M1: U1.1 (IP+), U$5.OUT_1 (OUT), U$5.OUT_2 (OUT)
V_BATT_M2: U4.1 (IP+), U$10.OUT_1 (OUT), U$10.OUT_2 (OUT)
V_BATT_M3: U6.1 (IP+), U$11.OUT_1 (OUT), U$11.OUT_2 (OUT)
V_BATT_M4: U8.1 (IP+), U$14.OUT_1 (OUT), U$14.OUT_2 (OUT)
V_BATT_M5: U12.1 (IP+), U$17.OUT_1 (OUT), U$17.OUT_2 (OUT)
V_BATT_M6: U14.1 (IP+), U$21.OUT_1 (OUT), U$21.OUT_2 (OUT)
V_BATT_M7: U17.1 (IP+), U$25.OUT_1 (OUT), U$25.OUT_2 (OUT)

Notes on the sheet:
Primary voltage monitoring
Power conditioning capacitance
Power input
TIVA

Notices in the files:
2015/SpencePower/Arduino/pins_arduino.h:
Copyright (c) 2007 David A. Mellis
Public License along with this library; if not, write to the
Free Software Foundation, Inc., 59 Temple Place, Suite 330,
Boston, MA  02111-1307  USA
parts and their libraries:
SparkFun-DigitalIC: Licensing: Creative Commons ShareAlike 4.0 International - https://creativecommons.org/licenses/by-sa/4.0
SparkFun-Capacitors: Licensing: CC v3.0 Share-Alike You are welcome to use this library for commercial purposes.
